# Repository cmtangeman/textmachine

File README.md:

# TextMachine
CrankPhone SW/FW/HW/Mech
Notes on directory structure:

FW:

ArduinoILI9341MKNNB1500 :  All for resistive touch FW (old)

capTouchTestingAndCal: testing calibration of capacitive touch

receiveSMSwithDebug:  debug file that doesn't need touchscreen

techmach: FW for old resistive screen

techmachcap: FW for current working capacitive touch screen.  See README.txt in this directory for further info.

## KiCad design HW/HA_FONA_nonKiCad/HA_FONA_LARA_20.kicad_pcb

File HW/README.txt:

Herein lies the HW, including board design, BOM, physical design, etc.  

The plan is to delta from the known working feather FONA board and fit it into current CrankLite PCB form factor.
This would make the physical design changes minimal, though a few cleanups to the physical design may occur.

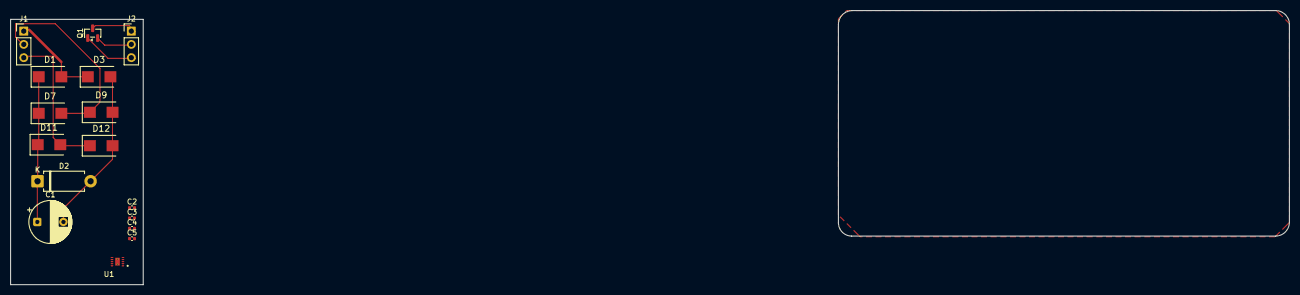
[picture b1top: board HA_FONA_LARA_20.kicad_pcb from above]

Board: 2 copper layers, 25.4 x 50.8 mm, 16 parts (0 on the bottom side), 9 nets.

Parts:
C1: C_Polarized; CP_Radial_D8.0mm_P5.00mm
C2: 2.2u; C_0402_1005Metric
C3: 0.1u; C_0402_1005Metric
C4: 10u; C_0402_1005Metric
C5: 1u; C_0402_1005Metric
D1, D3, D7, D9, D11, D12: DIODE; DIOM5336X265N
D2: D; D_DO-15_P10.16mm_Horizontal
J1, J2: Conn_01x03_Pin; PinHeader_1x03_P2.54mm_Vertical
Q1: PMOS; SOT-23
U1: BQ25185DLHR; IC_BQ25185DLHR

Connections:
GND: C1.2, C2.1, C3.1, C4.2, D2.2 (A), D3.2 (A), D9.2 (A), D12.2 (A), U1.5 (GND)
unnamed: D1.2 (A), D3.1 (C), J1.1
unnamed: D7.2 (A), D9.1 (C), J1.2
unnamed: D11.2 (A), D12.1 (C), J1.3
unnamed: J2.1, Q1.3 (S)
unnamed: J2.2, Q1.2 (G)
unnamed: J2.3, Q1.1 (D)
unnamed: C4.1, U1.1 (SYS)
VBAT: C1.1, C2.2, C3.2, D1.1 (C), D2.1 (K), D7.1 (C), D11.1 (C), U1.10 (IN)

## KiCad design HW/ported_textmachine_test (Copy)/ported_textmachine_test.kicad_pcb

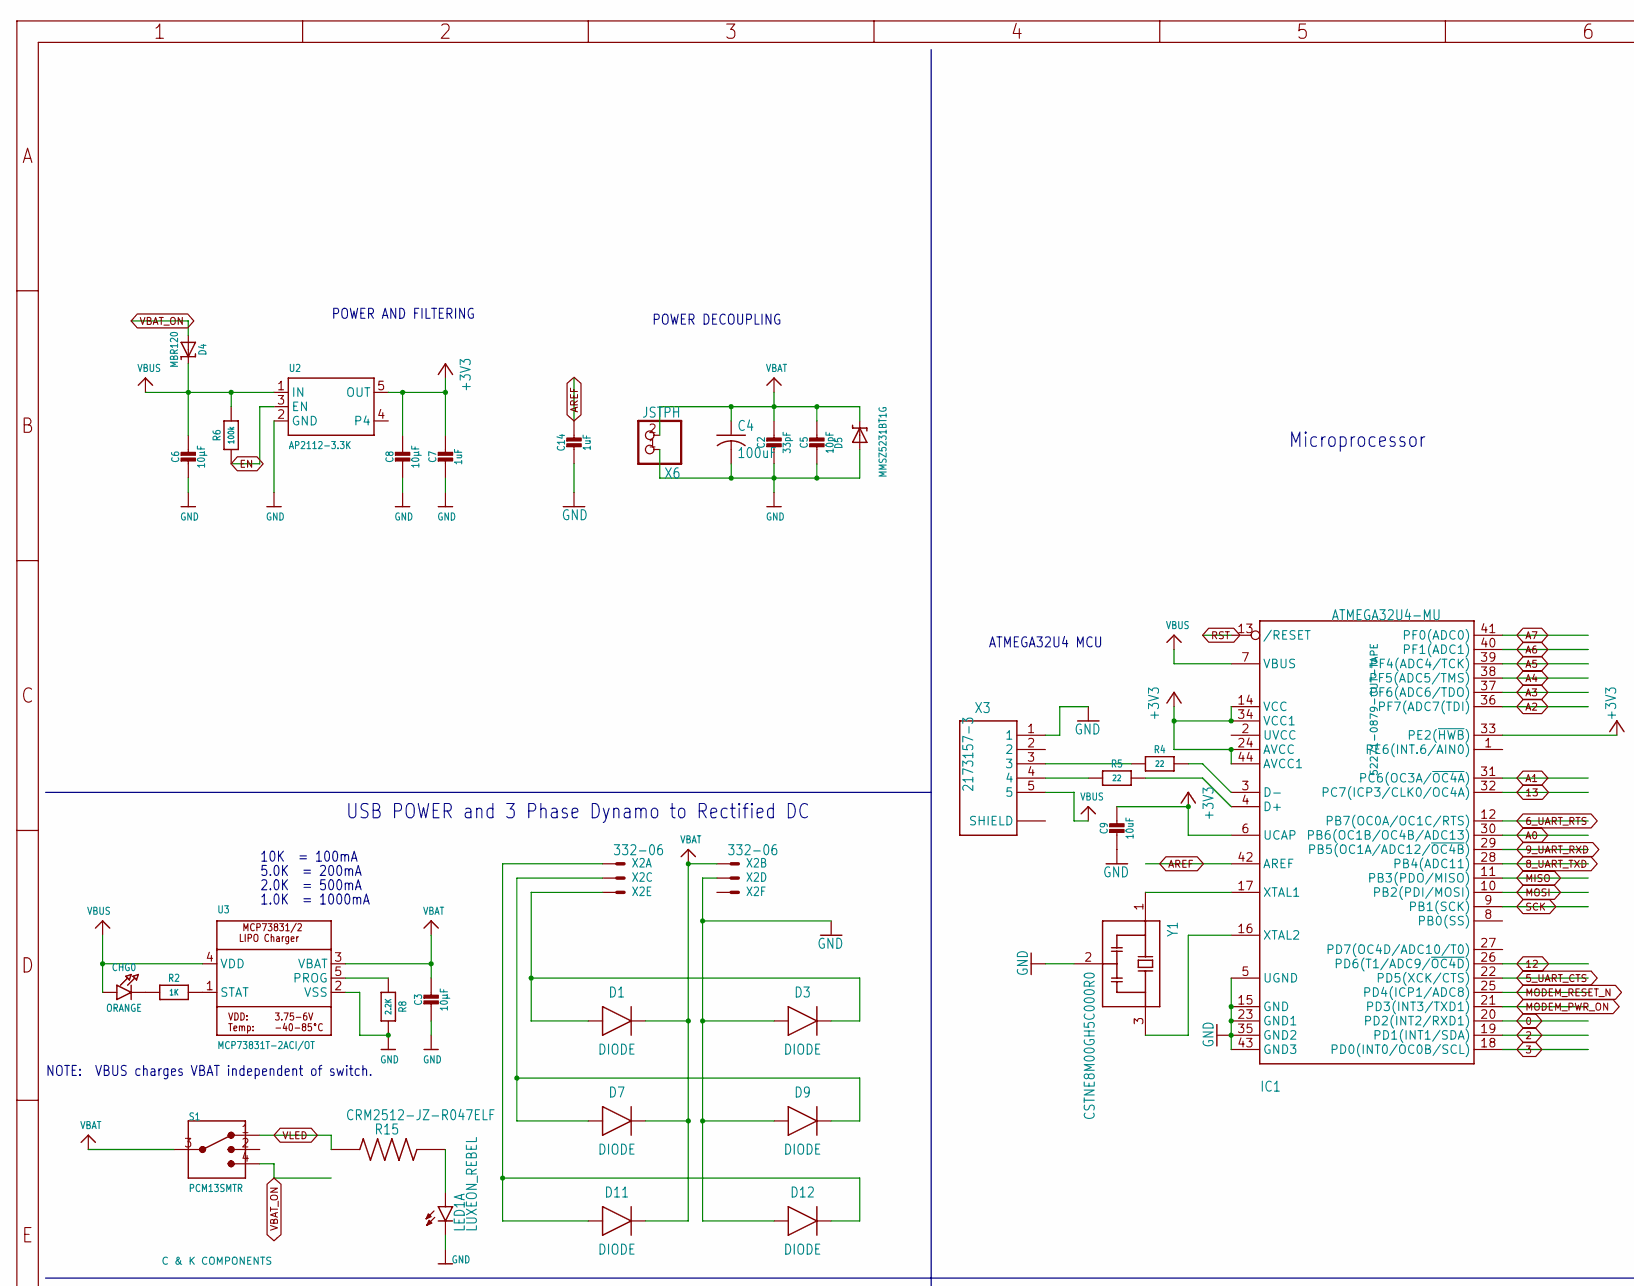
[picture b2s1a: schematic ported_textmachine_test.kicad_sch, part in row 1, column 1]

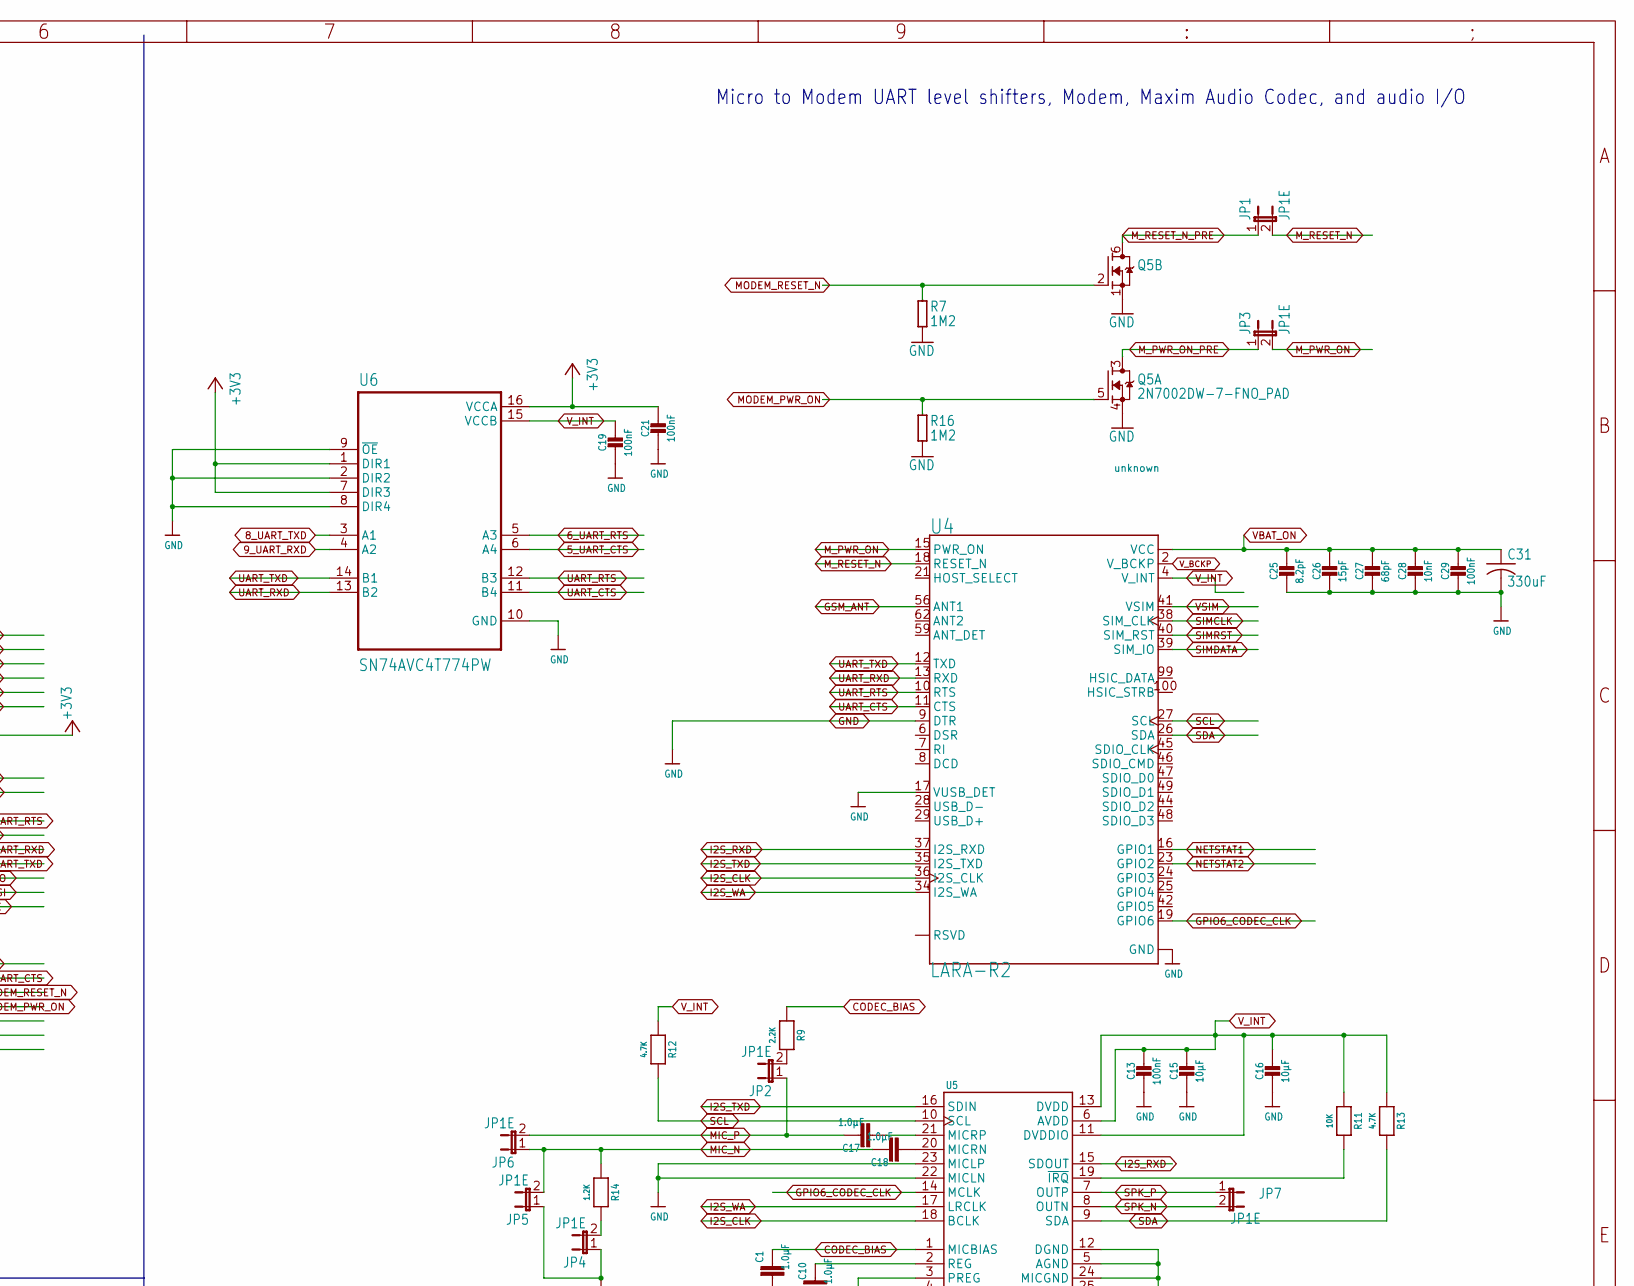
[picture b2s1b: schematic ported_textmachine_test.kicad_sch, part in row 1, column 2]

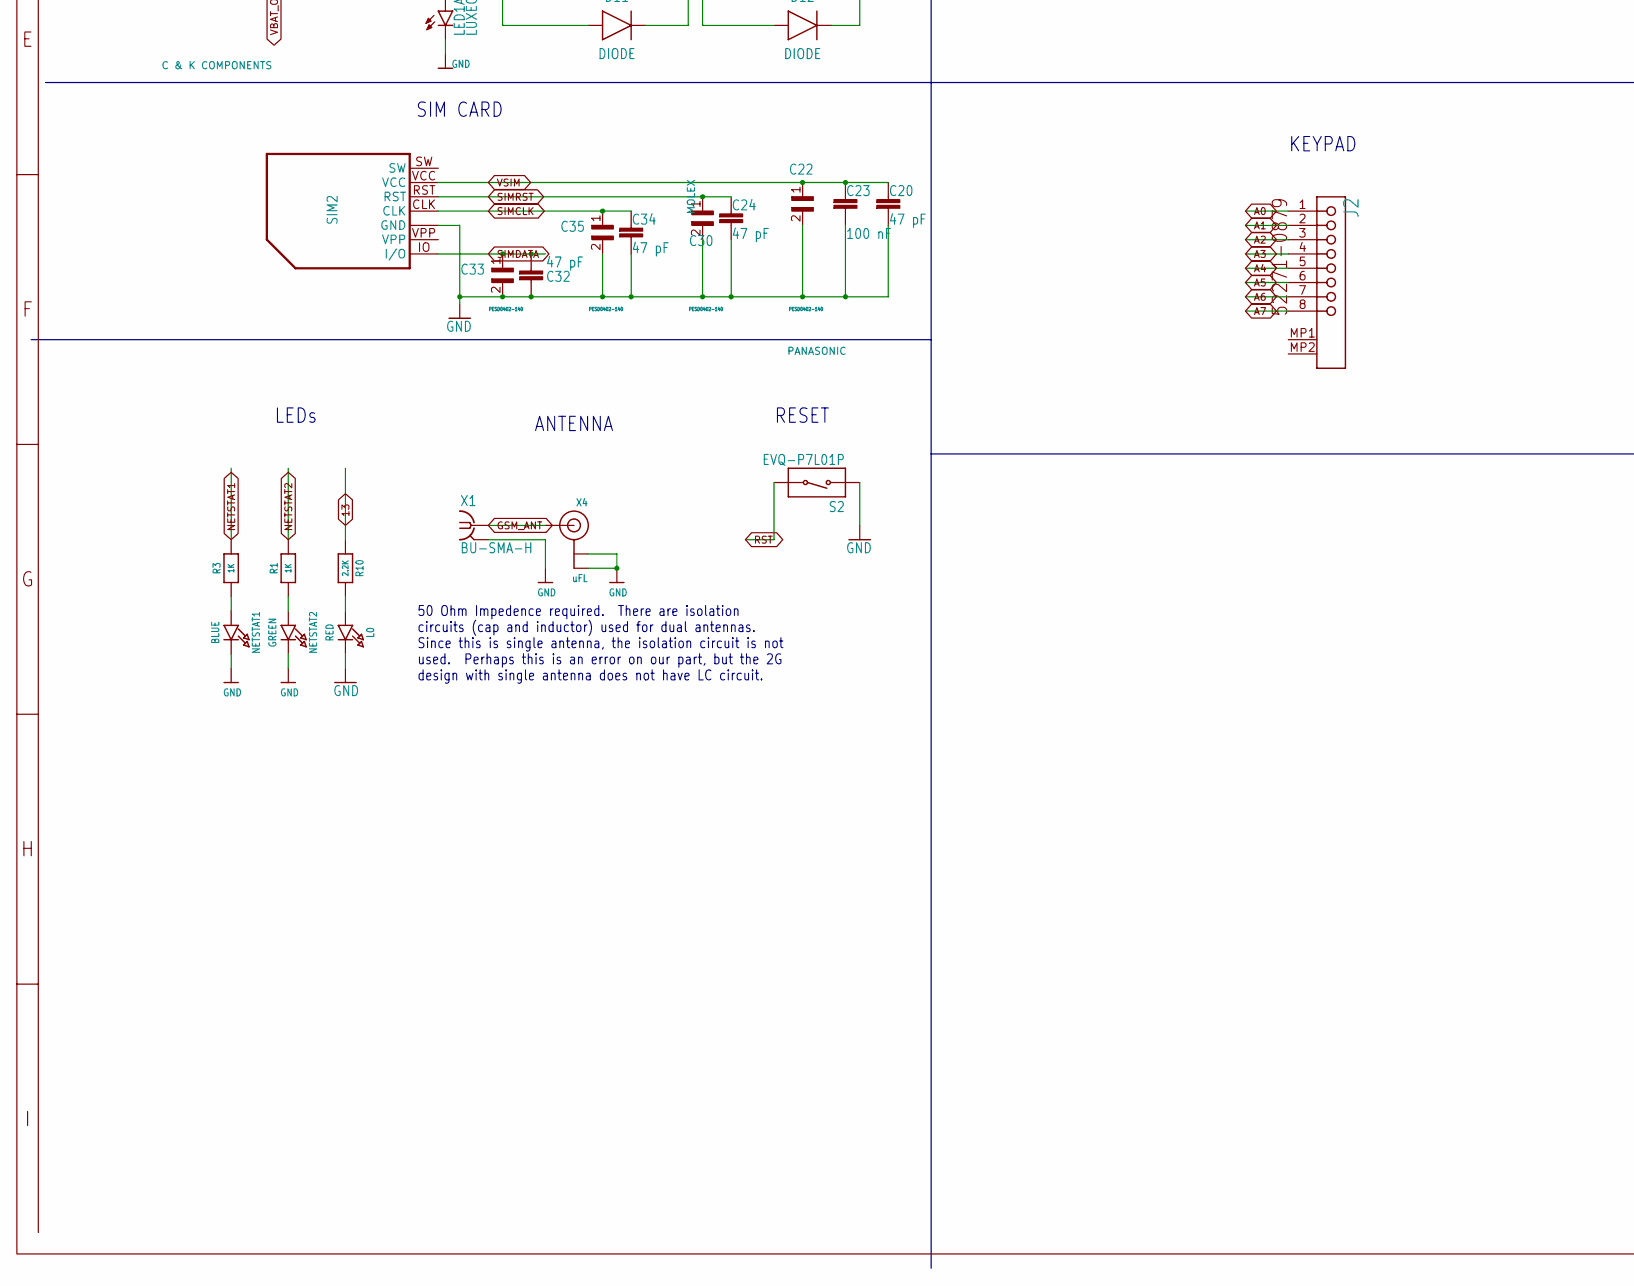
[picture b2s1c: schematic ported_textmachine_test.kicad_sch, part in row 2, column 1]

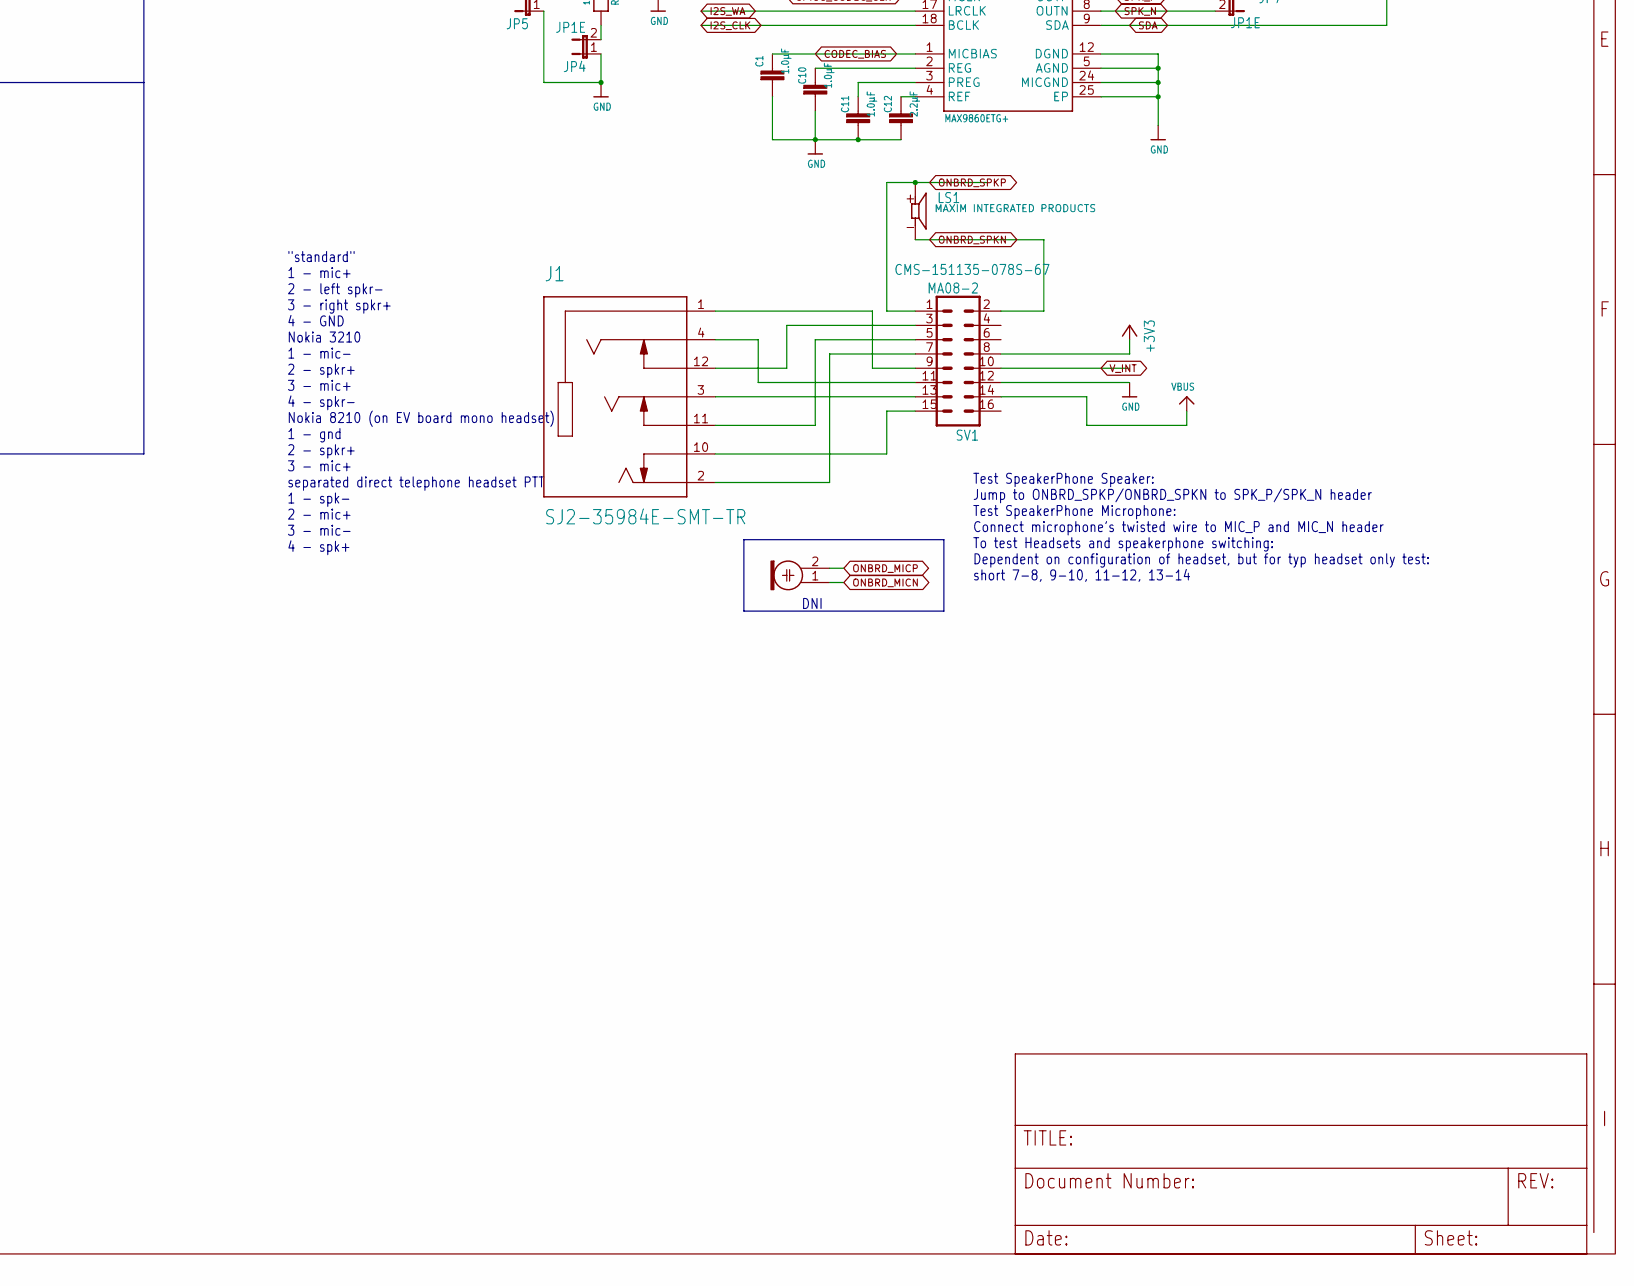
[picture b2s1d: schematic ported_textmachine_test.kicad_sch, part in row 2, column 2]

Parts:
C1: 1.0µF; CAPC1005X60; MPN T491A225K016AT
C2: 33pF; 0805-NO; MPN 04025A330JAT2A
C3, C6, C8, C15, C16: 10µF; 0805-NO; MPN 08053D106KAT2A
C4: 100uF; C1210; MPN C1210C107M8PACTU
C5: 10pF; 0805-NO; MPN C0805C100D5GACTU
C7, C14: 1uF; 0603-NO; MPN 02016D104KAT2A
C9: 10uF; _0805MP; MPN 08053D106KAT2A
C10, C11, C17, C18: 1.0µF; CAPC1005X60; MPN 02016D104KAT2A
C12: 2.2µF; CAPC1608X85; MPN T491A225K016AT
C13: 100nF; 0805-NO; MPN 08055C104KAT2A
C19, C21, C29: 100nF; _0402; MPN C1005X7R1C104K050BC
C20, C24, C32, C34: 47 pF; CAPC1005X60
C22, C30, C33, C35: PESD0402-140; RESC1005X35N
C23: 100 nF; CAPC1005X60
C25: 8.2pF; _0402; MPN NMC0402NPO8R2C50TRPF
C26: 15pF; _0402; MPN MCMT15N150F500CT
C27: 68pF; _0402; MPN C0603C680J3GACAUTO
C28: 10nF; _0402; MPN 06035C103KAT2A
C31: 330uF; C1210; MPN GRM32EC80E337ME05L
CHG0: ORANGE; CHIPLED_0805_NOOUTLINE; MPN KPT-2012SECK
D1, D3, D7, D9, D11, D12: DIODE; DIOM5336X265N
D4: MBR120; SOD-123; MPN MBR120VLSFT1G
D5: MMSZ5231BT1G; SOD-123; MPN MMSZ5231BT1G
IC1: ATMEGA32U4-MU; TQFN44_7MM; MPN ATMEGA32U4-MU
J1: SJ2-35984E-SMT-TR; CUI_SJ2-35984E-SMT-TR
J2: MOLEX_52271-0879MOLEX_52271-0879_0_0; MOLEX_52271-0879_0; VOLTAGE_MAX 50V AC (RMS)/DC; MPN 52271-0879
JP1, JP2, JP3, JP4, JP5, JP6, JP7: JP1E; JP1
L0: RED; MICROBUILDER_CHIPLED_0603; MPN KPT-1608LVSECK-J3-PRV
LED1: LUXEON_REBEL
LS1: CMS-151135-078S-67; SPKR_CMS-151135-078S-67; PARTREV 1.0
M2: ELECTRET_MICROPHON-WM-61A; WM-61A
NETSTAT1: BLUE; CHIPLED_0805_NOOUTLINE; MPN KPT-2012LVVBC-D
NETSTAT2: GREEN; CHIPLED_0805_NOOUTLINE; MPN KPT-2012ZGCK
Q5: 2N7002DW-7-FNO_PAD; PWR_SC70-6L2
R1, R2, R3: 1K; 0603-NO; MPN ERJ3EKF1001V
R4, R5: 22; 0603-NO
R6: 100k; 0603-NO; MPN MCWR06X1003FTL
R7, R16: 1M2; 0402-1005X55N; MPN MCHVR02FTFY1204
R8, R9, R10: 2.2K; 0603-NO; MPN RC0603FR-072K2L.
R11: 10K; 0603-NO; MPN CRCW060310K0FKEA
R12, R13: 4.7K; 0603-NO; MPN ERJ-3EKF4701V
R14: 1.2K; 0603-NO; MPN CRCW06031K20FKEA
R15: CRM2512-JZ-R047ELF; RESC6331X80N
S1: PCM13SMTR; SW_PCM13SMTR; MPN PCM13SMTR; DIGI-KEY_PART_NUMBER 401-2017-1-ND
S2: EVQ-P7L01P; SW_EVQ-P7L01P; MPN EVQP7L01P
SIM2: -; MICROSIM8
SV1: MA08-2
U2: AP2112-3.3K; SOT23-5
U3: MCP73831T-2ACI/OT; SOT23-5; MPN MCP73831T-2ACI/OT
U4: LARA-R2; XCVR_LARA-R2
U5: MAX9860ETG+; QFN50P400X400X75-25N; MPN MAX9860ETG+
U6: SN74AVC4T774PW; SOP65P640X120-16N
X1: BU-SMA-H
X2: 332-06
X3: 2173157-3; CONN_2173157-3
X4: uFL; U.FL; MPN U.FL-R-SMT-1(10)
X6: JSTPH; JSTPH2
Y1: CSTNE8M00GH5C000R0; OSC_CSTNE8M00GH5C000R0

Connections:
0: IC1.20 (PD2(INT2/RXD1))
2: IC1.19 (PD1(INT1/SDA))
3: IC1.18 (PD0(INT0/OC0B/SCL))
5_UART_CTS: IC1.22 (PD5(XCK/CTS)), U6.6 (A4)
6_UART_RTS: IC1.12 (PB7(OC0A/OC1C/RTS)), U6.5 (A3)
8_UART_TXD: IC1.28 (PB4(ADC11)), U6.3 (A1)
9_UART_RXD: IC1.29 (PB5(OC1A/ADC12/~OC4B)), U6.4 (A2)
12: IC1.26 (PD6(T1/ADC9/~OC4D))
13: IC1.32 (PC7(ICP3/CLK0/OC4A)), R10.1
+3V3: C7.1, C8.1, C9.1, C21.1, IC1.6 (UCAP), IC1.14 (VCC), IC1.24 (AVCC), IC1.33 (PE2(~HWB)), IC1.34 (VCC1), IC1.44 (AVCC1), SV1.8, U2.5 (OUT), U6.1 (DIR1), U6.7 (DIR3), U6.16 (VCCA)
A0: IC1.30 (PB6(OC1B/OC4B/ADC13)), J2.1
A1: IC1.31 (PC6(OC3A/~OC4A)), J2.2
A2: IC1.36 (PF7(ADC7(TDI)), J2.3
A3: IC1.37 (PF6(ADC6/TDO)), J2.4
A4: IC1.38 (PF5(ADC5/TMS)), J2.5
A5: IC1.39 (PF4(ADC4/TCK)), J2.6
A6: IC1.40 (PF1(ADC1)), J2.7
A7: IC1.41 (PF0(ADC0)), J2.8
AREF: C14.1, IC1.42 (AREF)
CODEC_BIAS: C1.1, R9.1, U5.1 (MICBIAS)
D+: IC1.4 (D+), R5.2
D-: IC1.3 (D-), R4.2
EN: R6.1, U2.3 (EN)
GND: C1.2, C2.2, C3.2, C4.2, C5.2, C6.2, C7.2, C8.2, C9.2, C10.2, C11.2, C12.2, C13.2, C14.2, C15.2, C16.2, C19.2, C20.2, C21.2, C22.2, C23.2, C24.2, C25.2, C26.2, C27.2, C28.2, C29.2, C30.2, C31.2, C32.2, C33.2, C34.2, C35.2, D3.2 (A), D5.A, D9.2 (A), D12.2 (A), IC1.5 (UGND), IC1.15 (GND), IC1.23 (GND1), IC1.35 (GND2), IC1.43 (GND3), JP4.1, JP5.1, L0.C, LED1.C, LED1.C@1 (C), NETSTAT1.C, NETSTAT2.C, Q5.1 (S), Q5.4 (S), R7.1, R8.2, R16.1, S2.1_1 (1), S2.1_2 (1), SIM2.GND, SIM2.SH1 (GND), SIM2.SH2 (GND), SIM2.SH3 (GND), SIM2.SH4 (GND), SIM2.SH5 (GND), SV1.12, U2.2 (GND), U3.2 (VSS), U4.1 (GND), U4.3 (GND), U4.5 (GND), U4.9 (DTR), U4.14 (GND), U4.17 (VUSB_DET), U4.20 (GND), U4.22 (GND), U4.30 (GND), U4.32 (GND), U4.43 (GND), U4.50 (GND), U4.54 (GND), U4.55 (GND), U4.57 (GND), U4.58 (GND), U4.60 (GND), U4.61 (GND), U4.63 (GND), U4.64 (GND), U4.65 (GND), U4.66 (GND), U4.67 (GND), U4.68 (GND), U4.69 (GND), U4.70 (GND), U4.71 (GND), U4.72 (GND), U4.73 (GND), U4.74 (GND), U4.75 (GND), U4.76 (GND), U4.77 (GND), U4.78 (GND), U4.79 (GND), U4.80 (GND), U4.81 (GND), U4.82 (GND), U4.83 (GND), U4.84 (GND), U4.85 (GND), U4.86 (GND), U4.87 (GND), U4.88 (GND), U4.89 (GND), U4.90 (GND), U4.91 (GND), U4.92 (GND), U4.93 (GND), U4.94 (GND), U4.95 (GND), U4.96 (GND), U5.5 (AGND), U5.12 (DGND), U5.22 (MICLN), U5.23 (MICLP), U5.24 (MICGND), U5.25 (EP), U6.2 (DIR2), U6.8 (DIR4), U6.9 (~OE), U6.10 (GND), X1.2, X1.3 (2), X1.4 (2), X1.5 (2), X2.4, X3.1, X4.1 (GND), X4.2 (GND), X6.1, Y1.2 (GND)
GPIO6_CODEC_CLK: U4.19 (GPIO6), U5.14 (MCLK)
GSM_ANT: U4.56 (ANT1), X1.1, X4.3 (SIGNAL)
I2S_CLK: U4.36 (I2S_CLK), U5.18 (BCLK)
I2S_RXD: U4.37 (I2S_RXD), U5.15 (SDOUT)
I2S_TXD: U4.35 (I2S_TXD), U5.16 (SDIN)
I2S_WA: U4.34 (I2S_WA), U5.17 (LRCLK)
MIC_N: C18.1, JP5.2, JP6.1, R14.1
MIC_P: C17.1, JP2.1, JP6.2
MISO: IC1.11 (PB3(PDO/MISO))
MODEM_PWR_ON: IC1.21 (PD3(INT3/TXD1)), Q5.5 (G), R16.2
MODEM_RESET_N: IC1.25 (PD4(ICP1/ADC8)), Q5.2 (G), R7.2
MOSI: IC1.10 (PB2(PDI/MOSI))
M_PWR_ON: JP3.2, U4.15 (PWR_ON)
M_PWR_ON_PRE: JP3.1, Q5.3 (D)
M_RESET_N: JP1.2, U4.18 (RESET_N)
M_RESET_N_PRE: JP1.1, Q5.6 (D)
unnamed: CHG0.C, R2.1
unnamed: L0.A, R10.2
unnamed: R2.2, U3.1 (STAT)
unnamed: R8.1, U3.5 (PROG)
unnamed: NETSTAT2.A, R1.1
unnamed: D11.2 (A), D12.1 (C), X2.1
unnamed: C17.2, U5.21 (MICRP)
unnamed: NETSTAT1.A, R3.1
unnamed: C12.1, U5.4 (REF)
unnamed: IC1.16 (XTAL2), Y1.3 (OUT)
unnamed: IC1.17 (XTAL1), Y1.1 (IN)
unnamed: C11.1, U5.3 (PREG)
unnamed: C10.1, U5.2 (REG)
unnamed: R5.1, X3.4
unnamed: R4.1, X3.3
unnamed: C18.2, U5.20 (MICRN)
unnamed: R11.2, U5.19 (~IRQ)
unnamed: JP2.2, R9.2
unnamed: JP4.2, R14.2
unnamed: D7.2 (A), D9.1 (C), X2.3
unnamed: D1.2 (A), D3.1 (C), X2.5
unnamed: J1.11 (RING1_SWITCH), SV1.5
unnamed: LED1.A, LED1.A@1 (A), R15.2
unnamed: J1.12 (RING2_SWITCH), SV1.3
unnamed: J1.2 (TIP), SV1.7
unnamed: J1.1 (SLEEVE), SV1.9
unnamed: J1.4 (RING2), SV1.11
unnamed: J1.3 (RING1), SV1.13
unnamed: J1.10 (TIP_SWITCH), SV1.15
NETSTAT1: R3.2, U4.16 (GPIO1)
NETSTAT2: R1.2, U4.23 (GPIO2)
ONBRD_MICN: M2.1
ONBRD_MICP: M2.2
ONBRD_SPKN: LS1.M, SV1.2
ONBRD_SPKP: LS1.P, SV1.1
RST: IC1.13 (/RESET), S2.2_1 (2), S2.2_2 (2)
SCK: IC1.9 (PB1(SCK))
SCL: R12.2, U4.27 (SCL), U5.10 (SCL)
SDA: R13.2, U4.26 (SDA), U5.9 (SDA)
SIMCLK: C34.1, C35.1, SIM2.CLK, U4.38 (SIM_CLK)
SIMDATA: C32.1, C33.1, SIM2.IO (I/O), U4.39 (SIM_IO)
SIMRST: C24.1, C30.1, SIM2.RST, U4.40 (SIM_RST)
SPK_N: JP7.2, U5.8 (OUTN)
SPK_P: JP7.1, U5.7 (OUTP)
UART_CTS: U4.11 (CTS), U6.11 (B4)
UART_RTS: U4.10 (RTS), U6.12 (B3)
UART_RXD: U4.13 (RXD), U6.13 (B2)
UART_TXD: U4.12 (TXD), U6.14 (B1)
VBAT: C2.1, C3.1, C4.1, C5.1, D1.1 (C), D5.C, D7.1 (C), D11.1 (C), S1.3, U3.3 (VBAT), X2.2, X6.2
VBAT_ON: C25.1, C26.1, C27.1, C28.1, C29.1, C31.1, D4.A, S1.4, U4.51 (VCC), U4.52 (VCC), U4.53 (VCC)
VBUS: C6.1, CHG0.A, D4.C, IC1.7 (VBUS), R6.2, SV1.14, U2.1 (IN), U3.4 (VDD), X3.5
VLED: R15.1, S1.1
VSIM: C20.1, C22.1, C23.1, SIM2.VCC, U4.41 (VSIM)
V_BCKP: U4.2 (V_BCKP)
V_INT: C13.1, C15.1, C16.1, C19.1, R11.1, R12.1, R13.1, SV1.10, U4.4 (V_INT), U5.6 (AVDD), U5.11 (DVDDIO), U5.13 (DVDD), U6.15 (VCCB)

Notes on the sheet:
Microprocessor
POWER DECOUPLING
KEYPAD
Micro to Modem UART level shifters, Modem, Maxim Audio Codec, and audio I/O
2.0K = 500mA
1.0K = 1000mA
LEDs
50 Ohm Impedence required. There are isolation circuits (cap and inductor) used for dual antennas. Since this is single antenna, the isolation circuit is not used. Perhaps this is an error on our part, but the 2G design with single antenna does not have LC circuit.
SIM CARD
RESET
5.0K = 200mA
DNI
NOTE: VBUS charges VBAT independent of switch.
Test SpeakerPhone Speaker: Jump to ONBRD_SPKP/ONBRD_SPKN to SPK_P/SPK_N header Test SpeakerPhone Microphone: Connect microphone's twisted wire to MIC_P and MIC_N header To test Headsets and speakerphone switching: Dependent on configuration of headset, but for typ headset only test: short 7-8, 9-10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
USB POWER and 3 Phase Dynamo to Rectified DC
POWER AND FILTERING
ANTENNA
ATMEGA32U4 MCU
"standard" 1 - mic+ 2 - left spkr- 3 - right spkr+ 4 - GND Nokia 3210 1 - mic- 2 - spkr+ 3 - mic+ 4 - spkr- Nokia 8210 (on EV board mono headset) 1 - gnd 2 - spkr+ 3 - mic+ separated direct telephone headset PTT 1 - spk- 2 - mic+ 3 - mic- 4 - spk+
10K = 100mA

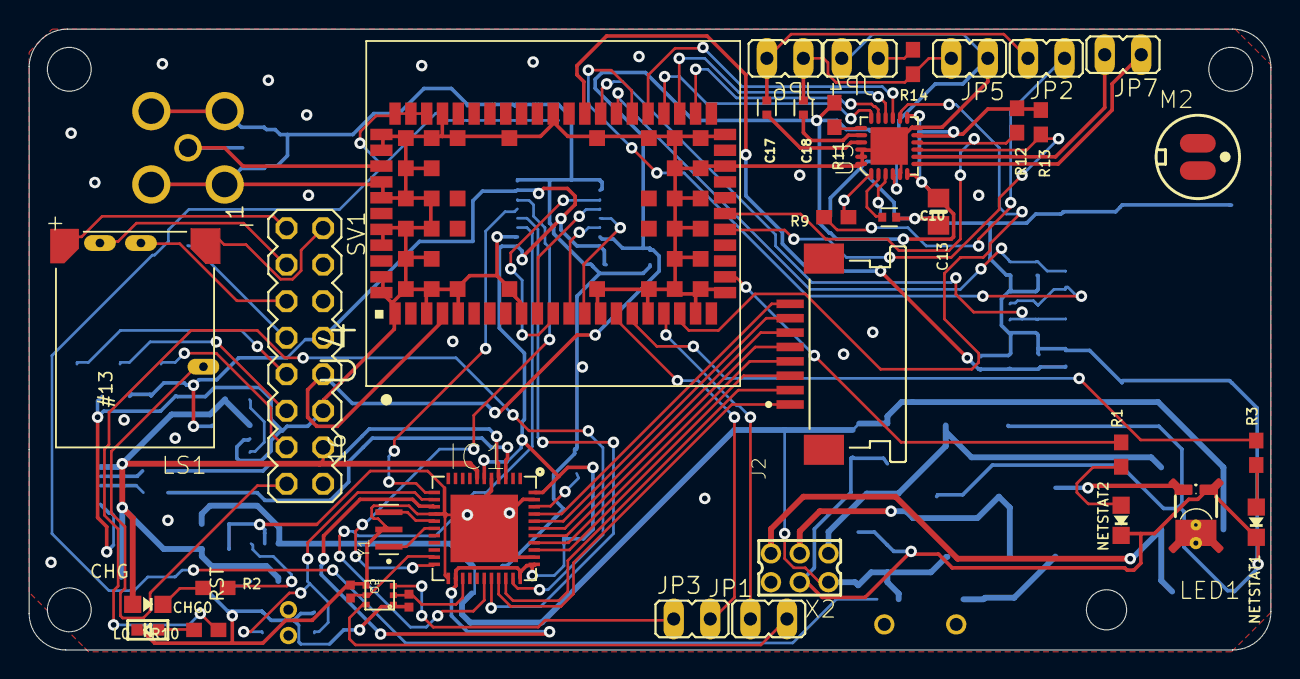
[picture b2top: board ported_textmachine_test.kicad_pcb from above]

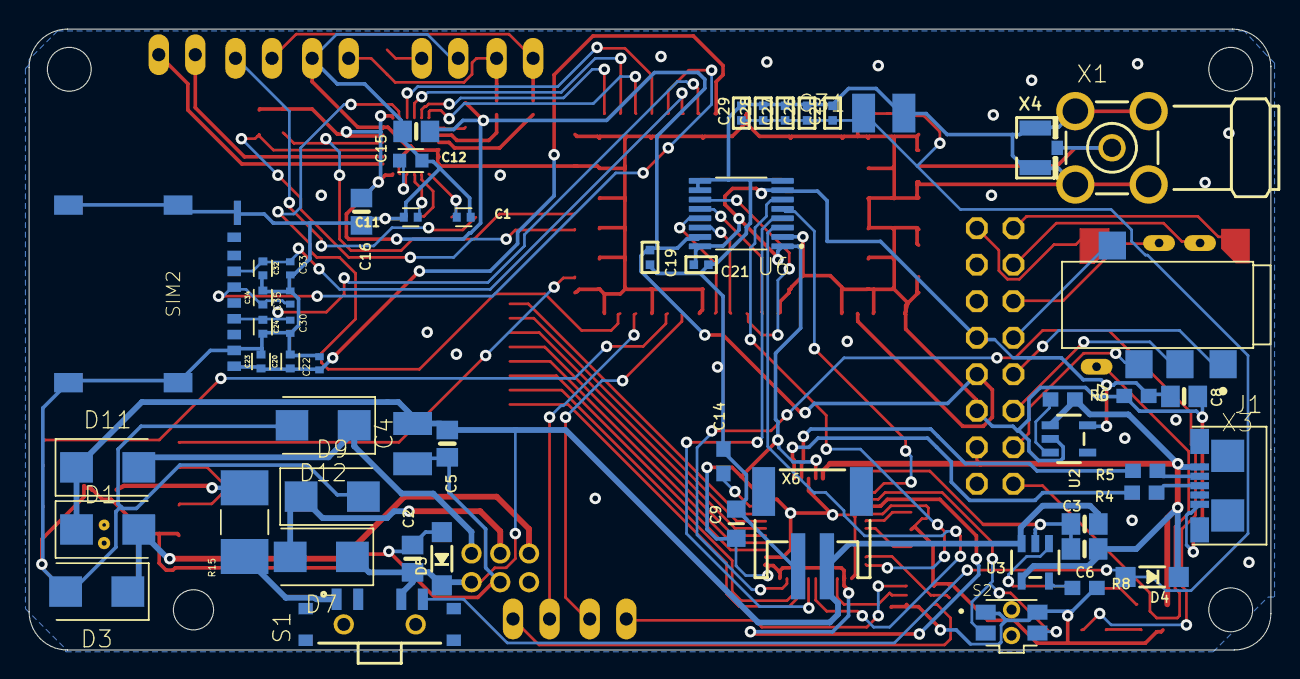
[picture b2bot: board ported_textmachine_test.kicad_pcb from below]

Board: 2 copper layers, 86.4 x 43.2 mm, 96 parts (55 on the bottom side), 85 nets.

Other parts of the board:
UNK_HOLE_0: dummyfp0
UNK_HOLE_1: dummyfp1
UNK_HOLE_2: dummyfp2
UNK_HOLE_3: dummyfp3

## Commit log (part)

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2026-01-21 Inital commit
2026-01-31 Removed crankphone stuff, creating a cleaner repository with just text machine stuff
2026-02-06 Adding csv with components descriptioins
2026-02-06 Organizing
2026-02-07 Serial logic done, transferring to tft
2026-02-11 Working touchscreen / display functionalllity
2026-02-14 Keyboard progress
2026-02-15 More keyboard progess, first text through GUI sent
2026-02-16 Keyboard sending texts, working through receive function, beggining implemtntationa of recent messages, contacs, once thats solidified move on to SD memory saving
2026-02-17 Implementation of recent messages UI
2026-02-25 Improvements to touchscreen detection keyboard (1hr)
2026-02-26 Fixed 0,0 garbage reading by adding new debouncing logic
2026-02-26 Added new UI_COMPOSE logic such that SEND is no longer the transition variable between msg input and phone number input, instead use standard method of clicking between the two input boxes to switch 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
2026-03-14 Added fonts, new keyboard, karat
2026-03-15 Reworking Messages and conversation modules, fixed touch bleedthrough for conversation and messages
2026-04-02 Added documentation - Design idea is to go off of crankLight altering the dimensions to match the TFT LCD touchscreen
2026-05-03 Create README.txt
    bit of description of files.
2026-05-03 Added PSM logic and install dependencies text file
2026-05-18 Added timestamp logic for messages and cleand up message thread logic. TODO for tommmorow: implement contact logic using serial monitor and SD card non volatile memory storage with csv file [4 hours]
2026-05-19 Added homescreen clock and CSQ RSSI meter for home screen as well, timestamp logic still needs to be cleaned up
2026-06-23 Added # checking to ensure e.164 format so no duplicate conversation
2026-06-26 Added contact name check in compose step
2026-06-29 Added scrolling functionality for contacts screen
